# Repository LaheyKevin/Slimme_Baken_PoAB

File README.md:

# Slimme Baken voor PoAB

## Documentatie

Beste lezer van dit document u kan de documentatie vinden door op volgende link te drukken. [documentatie baken](https://github.com/LaheyKevin/Slimme_Baken_PoAB/blob/main/Documentatie_PoAB_SlimmeBaken.docx)

## Deelnemers

 - Kevin Lahey
 - Quinten Moons

## Bronnen

[Mark down guide](https://www.markdownguide.org/cheat-sheet/)

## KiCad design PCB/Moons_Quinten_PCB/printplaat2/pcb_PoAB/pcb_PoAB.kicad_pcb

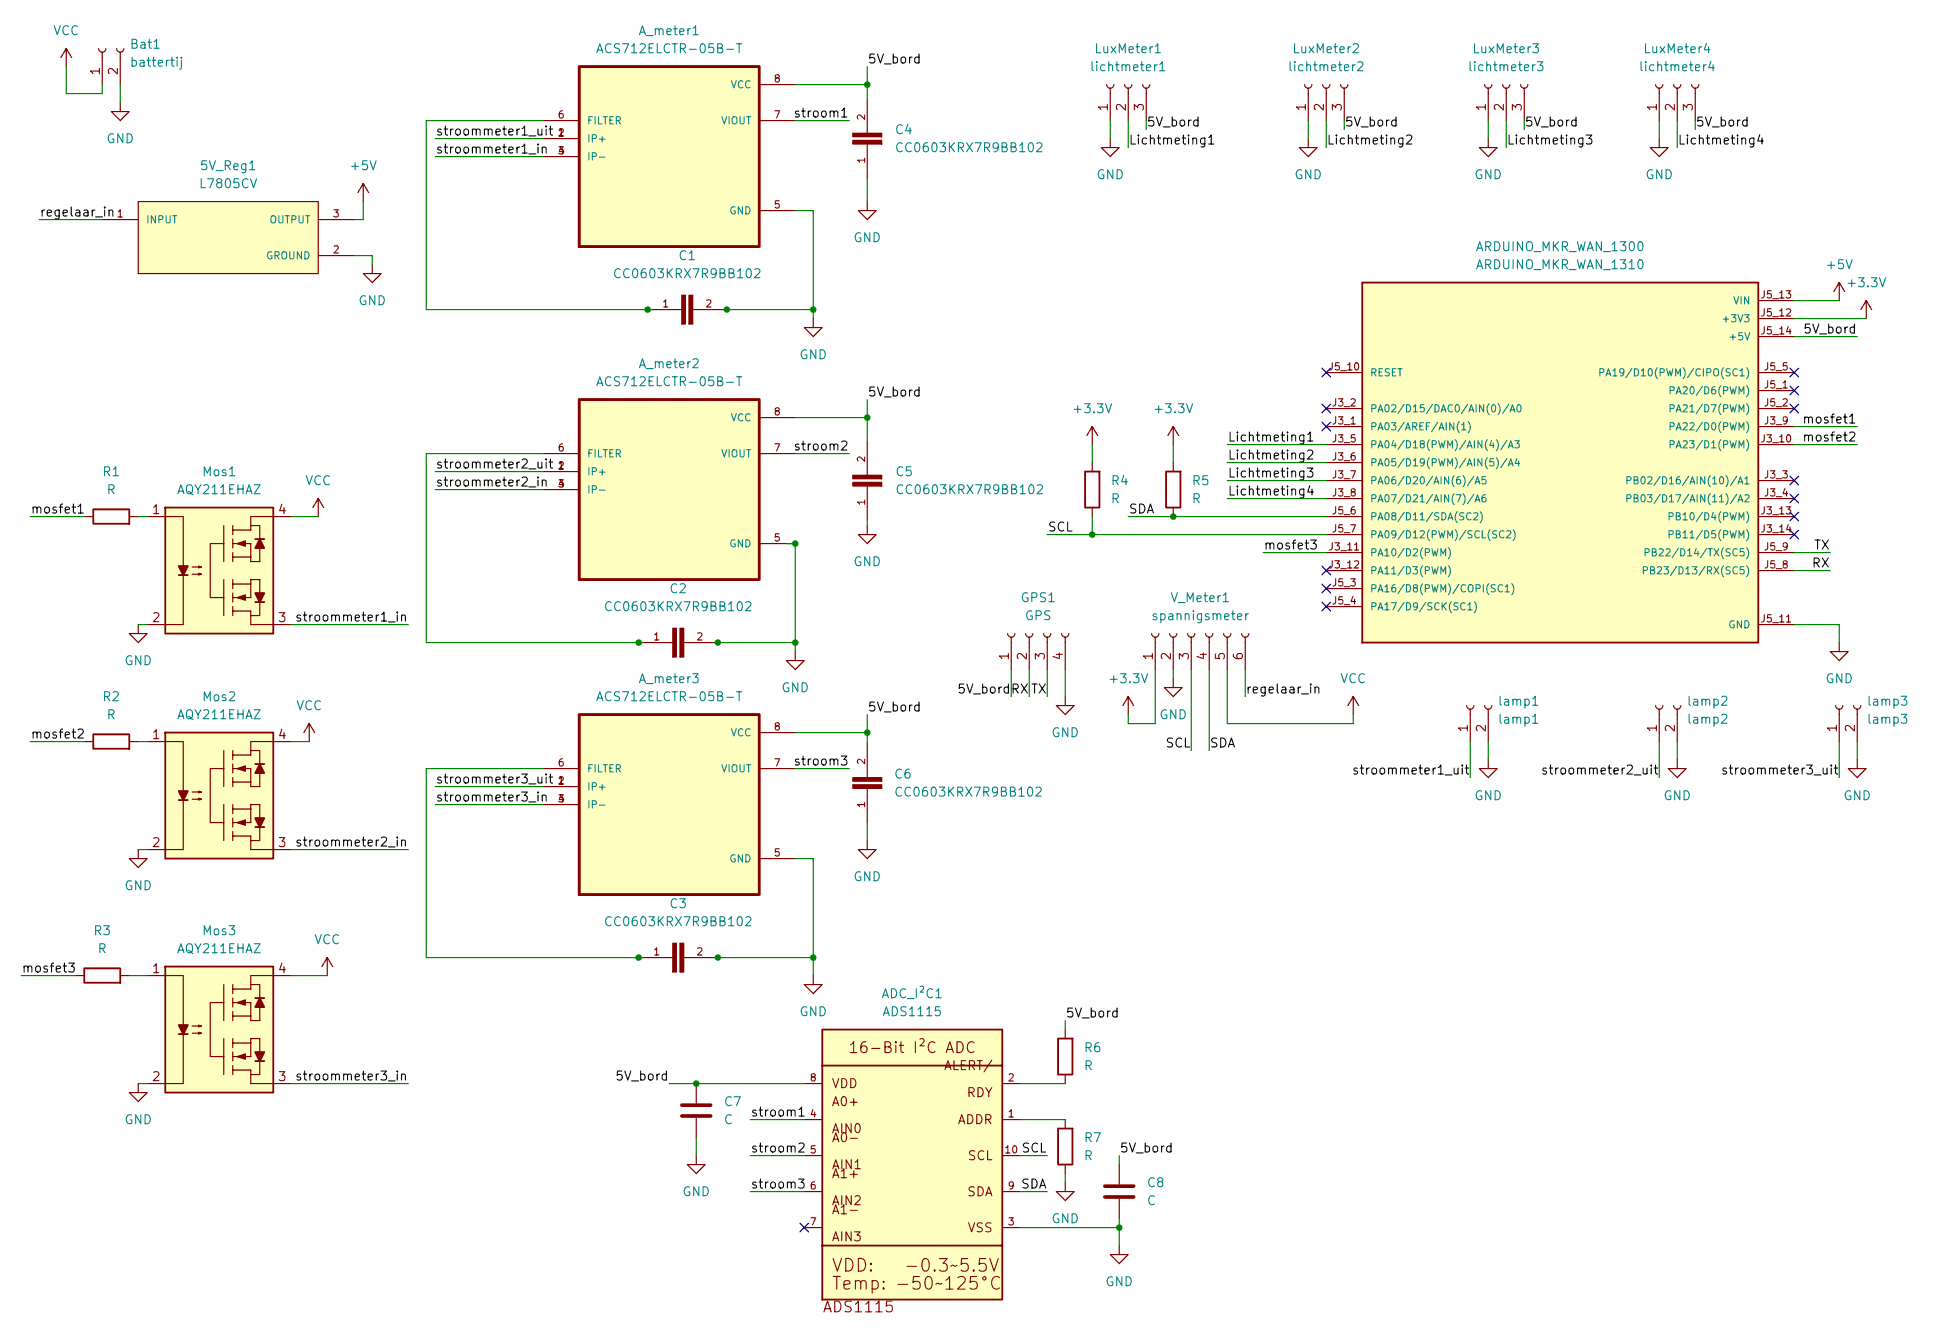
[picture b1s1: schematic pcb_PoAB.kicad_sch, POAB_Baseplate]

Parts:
5V_Reg1: L7805CV; TO255P1040X460X1968-3; PARTREV 36
ADC_I²C1: ADS1115; MSOP10
ARDUINO_MKR_WAN_1300: ARDUINO_MKR_WAN_1310; BOARD_ARDUINO_MKR_WAN_1310; PARTREV 06/27/2019
A_meter1, A_meter2, A_meter3: ACS712ELCTR-05B-T; SOIC127P600X175-8N
Bat1: battertij; PinSocket_1x02_P2.54mm_Vertical
C1, C2, C3, C4, C5, C6: CC0603KRX7R9BB102; CAPC1608X90
C7, C8: C; C_0805_2012Metric_Pad1.18x1.45mm_HandSolder
GPS1: GPS; PinSocket_1x04_P2.54mm_Vertical
LuxMeter1: lichtmeter1; PinSocket_1x03_P2.54mm_Vertical
LuxMeter2: lichtmeter2; PinSocket_1x03_P2.54mm_Vertical
LuxMeter3: lichtmeter3; PinSocket_1x03_P2.54mm_Vertical
LuxMeter4: lichtmeter4; PinSocket_1x03_P2.54mm_Vertical
Mos1, Mos2, Mos3: AQY211EHAZ
R1, R2, R3, R4, R5, R6, R7: R; R_0805_2012Metric_Pad1.20x1.40mm_HandSolder
V_Meter1: spannigsmeter; PinSocket_1x06_P2.54mm_Vertical
lamp1: lamp1; PinSocket_1x02_P2.54mm_Vertical
lamp2: lamp2; PinSocket_1x02_P2.54mm_Vertical
lamp3: lamp3; PinSocket_1x02_P2.54mm_Vertical

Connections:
+3.3V: ARDUINO_MKR_WAN_1300.J5_12 (+3V3), R4.2, R5.2, V_Meter1.1
+5V: 5V_Reg1.3 (OUTPUT), ARDUINO_MKR_WAN_1300.J5_13 (VIN)
/5V_bord: ADC_I²C1.8, ARDUINO_MKR_WAN_1300.J5_14 (+5V), A_meter1.8 (VCC), A_meter2.8 (VCC), A_meter3.8 (VCC), C4.2, C5.2, C6.2, C7.1, C8.1, GPS1.1, LuxMeter1.3, LuxMeter2.3, LuxMeter3.3, LuxMeter4.3, R6.2
/Lichtmeting1: ARDUINO_MKR_WAN_1300.J3_5 (PA04/D18(PWM)/AIN(4)/A3), LuxMeter1.2
/Lichtmeting2: ARDUINO_MKR_WAN_1300.J3_6 (PA05/D19(PWM)/AIN(5)/A4), LuxMeter2.2
/Lichtmeting3: ARDUINO_MKR_WAN_1300.J3_7 (PA06/D20/AIN(6)/A5), LuxMeter3.2
/Lichtmeting4: ARDUINO_MKR_WAN_1300.J3_8 (PA07/D21/AIN(7)/A6), LuxMeter4.2
/RX: ARDUINO_MKR_WAN_1300.J5_8 (PB23/D13/RX(SC5)), GPS1.2
/SCL: ADC_I²C1.10, ARDUINO_MKR_WAN_1300.J5_7 (PA09/D12(PWM)/SCL(SC2)), R4.1, V_Meter1.3
/SDA: ADC_I²C1.9, ARDUINO_MKR_WAN_1300.J5_6 (PA08/D11/SDA(SC2)), R5.1, V_Meter1.4
/TX: ARDUINO_MKR_WAN_1300.J5_9 (PB22/D14/TX(SC5)), GPS1.3
/mosfet1: ARDUINO_MKR_WAN_1300.J3_9 (PA22/D0(PWM)), R1.1
/mosfet2: ARDUINO_MKR_WAN_1300.J3_10 (PA23/D1(PWM)), R2.1
/mosfet3: ARDUINO_MKR_WAN_1300.J3_11 (PA10/D2(PWM)), R3.1
/regelaar_in: 5V_Reg1.1 (INPUT), V_Meter1.6
/stroom1: ADC_I²C1.4, A_meter1.7 (VIOUT)
/stroom2: ADC_I²C1.5, A_meter2.7 (VIOUT)
/stroom3: ADC_I²C1.6, A_meter3.7 (VIOUT)
/stroommeter1_in: A_meter1.3 (IP-), A_meter1.4 (IP-), Mos1.3 (VEE)
/stroommeter1_uit: A_meter1.1 (IP+), A_meter1.2 (IP+), lamp1.1
/stroommeter2_in: A_meter2.3 (IP-), A_meter2.4 (IP-), Mos2.3 (VEE)
/stroommeter2_uit: A_meter2.1 (IP+), A_meter2.2 (IP+), lamp2.1
/stroommeter3_in: A_meter3.3 (IP-), A_meter3.4 (IP-), Mos3.3 (VEE)
/stroommeter3_uit: A_meter3.1 (IP+), A_meter3.2 (IP+), lamp3.1
GND: 5V_Reg1.2 (GROUND), ADC_I²C1.3, ARDUINO_MKR_WAN_1300.J5_11 (GND), A_meter1.5 (GND), A_meter2.5 (GND), A_meter3.5 (GND), Bat1.2, C1.2, C2.2, C3.2, C4.1, C5.1, C6.1, C7.2, C8.2, GPS1.4, LuxMeter1.1, LuxMeter2.1, LuxMeter3.1, LuxMeter4.1, Mos1.2 (C), Mos2.2 (C), Mos3.2 (C), R7.1, V_Meter1.2, lamp1.2, lamp2.2, lamp3.2
unnamed: ADC_I²C1.1, R7.2
unnamed: ADC_I²C1.2, R6.1
unnamed: A_meter1.6 (FILTER), C1.1
unnamed: A_meter2.6 (FILTER), C2.1
unnamed: A_meter3.6 (FILTER), C3.1
unnamed: Mos1.1 (A), R1.2
unnamed: Mos2.1 (A), R2.2
unnamed: Mos3.1 (A), R3.2
VCC: Bat1.1, Mos1.4 (VCC), Mos2.4 (VCC), Mos3.4 (VCC), V_Meter1.5

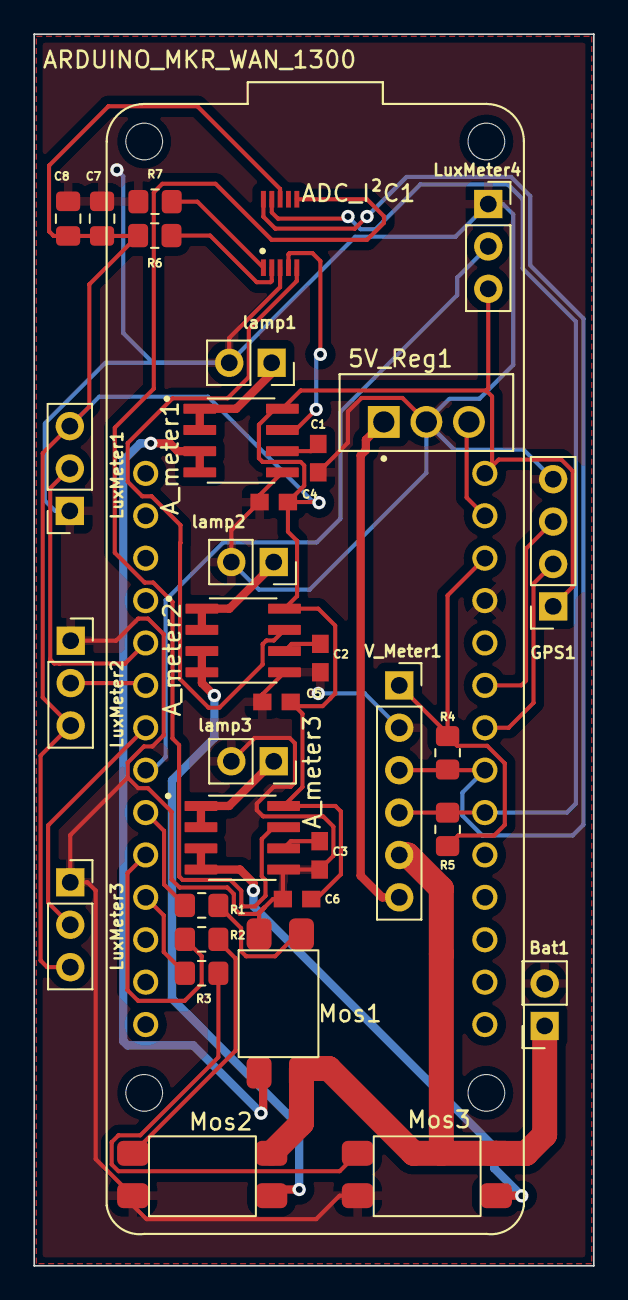
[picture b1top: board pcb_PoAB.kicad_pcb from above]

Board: 2 copper layers, 33.5 x 73.8 mm, 34 parts (0 on the bottom side), 34 nets.

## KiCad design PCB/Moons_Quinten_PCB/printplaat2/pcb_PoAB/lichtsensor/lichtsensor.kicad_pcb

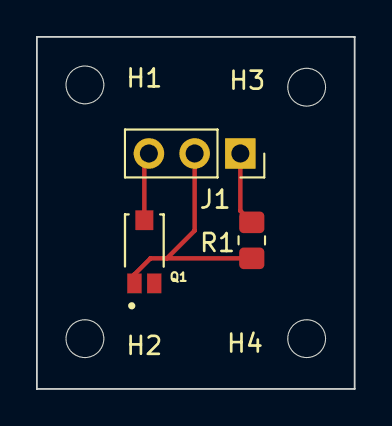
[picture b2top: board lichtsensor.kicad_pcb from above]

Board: 2 copper layers, 17.7 x 19.6 mm, 7 parts (0 on the bottom side), 3 nets.

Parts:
H1, H2, H3, H4: MountingHole_Pad; MountingHole_2.1mm
J1: Conn_01x03_Male; PinSocket_1x03_P2.54mm_Vertical
Q1: TEMT6000X01; TRANS_TEMT6000X01
R1: 10K; R_0805_2012Metric_Pad1.20x1.40mm_HandSolder

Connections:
/output: J1.2, Q1.1, R1.1
GND: J1.1, R1.2
VCC: J1.3, Q1.3

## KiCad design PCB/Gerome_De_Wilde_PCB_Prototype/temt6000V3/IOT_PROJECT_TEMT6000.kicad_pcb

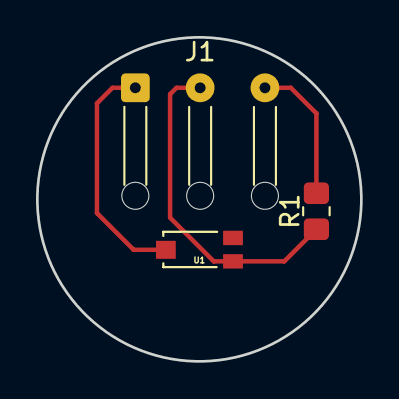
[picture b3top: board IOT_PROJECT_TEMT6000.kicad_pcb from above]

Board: 2 copper layers, 18.0 x 18.0 mm, 3 parts (0 on the bottom side), 3 nets.

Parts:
J1: Conn_01x03_Male; SolderWire-0.1sqmm_1x03_P3.6mm_D0.4mm_OD1mm_Relief
R1: R10K; R_0805_2012Metric_Pad1.20x1.40mm_HandSolder
U1: TEMT6000; TEMT6000-SEN

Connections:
GND: J1.3, R1.2
SIGNAL: J1.2, R1.1, U1.EMITTER
VCC: J1.1, U1.COLLECTOR

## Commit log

2023-02-16 update layout
2023-02-18 add bestellijst
2023-02-18 Push doc
2023-03-06 update picture
2023-03-06 toevoegen code
2023-03-06 testing en documentatie
2023-03-06 Data analyze
2023-03-06 Fix photo
2023-03-06 update stromen
2023-03-12 update klassen
2023-03-13 add pcb
2023-03-13 Onderzoek ssr/mosfet/relais
2023-03-15 aanpassing doc
2023-03-20 docs en gps-code aangepast + lichtmeting-code
2023-03-20 update docs
2023-03-20 strrommeting + libraries pcb + schema
2023-04-06 schema en pcb voor lichtsmeter en base
2023-04-09 pcb lichsensor toegevoegd
2023-04-16 lichtmetingen en voltage metingen toegevoegd
2023-04-16 spanningsmeter aangepast
2023-04-17 pcb gemaakt
2023-04-17 lichtmeting met temt6000 code
2023-04-22 update documentatie
2023-04-24 printplaat aangepast
2023-04-24 spannings meting en bord spanning aangepast pcb en schema
2023-04-25 PCB en schema spanning en stroommetingen aangepast
2023-04-25 pcb en spanningsmeting
2023-05-08 stoommeting codes gemaakt, spanningsmeting code aangepast en documentatie verder afgewerkt
2023-05-09 stroometingen en zips
2023-05-09 stroommeting met I2C
2023-05-14 schema aangepast
2023-05-15 schema baseplate aangepast
2023-05-15 pcb baseplate aangepast
2023-05-17 pcb zip gemaakt
2023-05-24 PCB track width adjusted
2023-05-30 printplaat baseplate tracks aangepast
2023-06-05 cleanup github
2023-06-05 Rename Documentatie_Kevin.md to Documentatie_Kevin_Oud.md
2023-06-07 printplaat en lichtmeter aangepast
2023-06-07 documenten aangepast
2023-06-07 pcb baseplate en docs aangepast
2023-06-07 pcb lichtsensor aangepast
2023-06-07 update github+documentatie
2023-06-08 add fotos
2023-06-08 documentatie aangepast
